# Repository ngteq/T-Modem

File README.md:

# T-Modem > USB-5V|12-Volt Terminal-Modem Reference
**Non-Profit for the Radio-World and easy to deploy/repair is parted by AI-Services**<br>
<br><br>

<br>

> **No firmware / no host software yet** — trees under `firmware/` and `software/` are placeholders only.  
> **Build a working hardware prototype first** (rails, assembly, bench checks).
> KiCad PCB is for **learning-by-doing** and small-run fab — run **DRC** and fix reported issues before ordering boards.  

**T-Modem** = **Terminal-Modem** — a real packet-radio modem board (registers + firmware) for host stacks such as MAX25-Stack.

**PHY mark:** **T-Modem-c12s24** — **c12** = chip **1200** (TCM3105-class AFSK) · **s24** = software **2400** (Pico firmware DSP later). One board; **no** second 2400 modem IC.

**Version:** **0.25** — hardware-only standard reference (**baseline** while building toward **v1.0**; software after the build) · [docs/HARDWARE-BASELINE.md](docs/HARDWARE-BASELINE.md)  
**License:** [GNU GPLv3](LICENSE)  
**Project intent:** non-profit / non-commercial community hardware project under GPLv3 (no separate legal entity claimed here).

**AS-IS — no support, no warranty:** This project and all materials are provided **as-is**. There is **no support** and **no warranty** of any kind. GPLv3 already disclaims warranty; this is also **project policy**.

**Scope:** T-Modem is a **standard reference only**. Custom product lines, per-customer variants, or commercial SKUs beyond that reference are **not** T-Modem — they are separate projects.

**Status/State:** The **v0.25** hardware design is **not** being redesigned. Develop it **as-is** to **v1.0** by **building** the board; **firmware / software come after** that. Change HW only if the build proves a blocking error.

Product docs and repo practice follow the operator publication standard (KISS, technical-right only, GPLv3 non-profit). This repository holds the complete product (hardware, firmware, shipped docs).

**Git branch:** you are on **`c12s24`** (active product tree). GitHub **`main`** is an index only — see [BRANCHES.md](BRANCHES.md).

---

## v0.25 release (this tag)

| Ships | Does not ship |
|-------|----------------|
| BOM with preferred commodity candidates + longevity notes | Firmware / host software |
| Fabricable netlist + KiCad project (190×110 mm TH PCB) | Fab-verified Gerbers without DRC pass |
| PCB outline + placement + assembly notes | Invented radio mic pinouts |
| Power · USB-A · green LCD · Pico UF2 · **TCM3105-class AFSK IF**
| **Hobby-friendly soldering** (sockets + through-hole) | Reflow / fine-pitch SMD as the default path |

See [docs/RELEASE-v0.25.md](docs/RELEASE-v0.25.md) · [docs/v0.25-VERIFICATION.md](docs/v0.25-VERIFICATION.md) · [docs/BOM.md](docs/BOM.md) · [docs/SCHEMATIC.md](docs/SCHEMATIC.md) · [docs/PCB-ASSEMBLY.md](docs/PCB-ASSEMBLY.md) · [hardware/](hardware/).

**Firmware / software:** placeholders only — [firmware/README.md](firmware/README.md) · [software/README.md](software/README.md).

---

## Hobby-friendly soldering

v0.25 is aimed at **hand soldering for anyone who can solder reasonably well** — not only professional reflow lines. Goal: **best value for money**, socketed, replaceable parts.

| Practice | Intent |
|----------|--------|
| **DIP / module sockets** | Modem IC in a **16-pin DIP socket**; Pico and LCD on **2.54 mm female sockets** |
| **Through-hole first** | Resistors, diodes, LEDs, trimmers, USB-A, barrel jack, screw terminals — **TH** (cheap commodity packs) |
| **Pre-made cheap modules** | Pico (~few €), green 16×2 LCD module, MP1584-class buck module — plug in, no fine-pitch MCU soldering |
| **I²C LCD level shift** | 5 V LCD1602 I²C backpack ↔ Pico 3.3 V: BSS138-class 4-ch module (**LV=3.3 V** · **HV=5 V** · GND common) — see [docs/BOM.md](docs/BOM.md) `U_LVL` |
| **Not required** | Stencil reflow, QFN/BGA, expensive milled sockets, or SOIC as the only modem package |

Assembly and cheap-part notes: [docs/PCB-ASSEMBLY.md](docs/PCB-ASSEMBLY.md) · [docs/BOM.md](docs/BOM.md) · [docs/ORDERING-BUDGET.md](docs/ORDERING-BUDGET.md).

---

## Role

| This repo | Elsewhere |
|-----------|-----------|
| Complete T-Modem **standard reference**: hardware, (future) firmware, BOM/PCB, shipped docs | MAX25-Stack: **thin plugin only** later (discover / talk; host keeps AX.25 / KISS) |
| Board owns modem PHY + register file + thin KISS bridge (when FW exists)

**Settled scope**

| Item | Fact |
|------|------|
| Form | Rectangle **190 × 110 mm** (v0.25 outline; §0.26 larger OK) |
| Modulation | AFSK **1200** (TCM3105-class) + **2400** (MCU DSP, FW later) |
| Host link | USB 2.0 **Type A receptacle** (toward PC); no active hub required |
| Power | **USB-only OK**; barrel **12 V** + buck **optional** (on reference); USB OR; optional active hub / **5 V** into USB/OR rail |
| Display | HD44780-class **16×2** character LCD, **green backlight** (preferred) |
| MCU | **Raspberry Pi Pico** (RP2040), preferably **Pico H** on socketed headers — ROM **UF2** field flash |
| Modem IC | **TCM3105**-class Bell-202 in **DIP + socket**
| Assembly | **Hobby-friendly:** sockets + through-hole; see section above |
| Field flash | Via the **USB Type-A** port to the PC (when FW exists) |
| Layer split | Host owns AX.25; board = modem + thin KISS |
| Radio equipment | Screw-terminal AF/PTT labels only — **no** invented mic pinouts |

---

## Build

| Step | v0.25 status |
|------|----------------|
| Schematic / netlist | **Documented** — [docs/SCHEMATIC.md](docs/SCHEMATIC.md) |
| KiCad project | **Present** — [hardware/kicad/t-modem/](hardware/kicad/t-modem/) (KiCad ≥8; docs images via `scripts/render_docs_images.py`) |
| PCB outline / placement | **Documented** — [docs/PCB-ASSEMBLY.md](docs/PCB-ASSEMBLY.md) · [docs/PCB-LAYOUT.md](docs/PCB-LAYOUT.md) |
| BOM | **Candidates** — [docs/BOM.md](docs/BOM.md) · [hardware/bom/BOM.csv](hardware/bom/BOM.csv) |
| Verification | [docs/v0.25-VERIFICATION.md](docs/v0.25-VERIFICATION.md) |
| Firmware tree | **Placeholder only** |
| Fab | **DRC clean** → export Gerbers — see [hardware/fab/README.md](hardware/fab/README.md). Personal small-run OK — **AS-IS** |

---

## Operate

| Topic | Status |
|-------|--------|
| Host attach (USB CDC/ACM) | **TBD** until firmware |
| Register map / KISS | **TBD** — see [docs/OVERVIEW.md](docs/OVERVIEW.md) |
| Radio cable / pinout per model | **TBD** — expand from verified notes only |
| RX before live TX | Operator practice when RF path exists |

Site-private secrets belong in `./local/` (gitignored) — never commit passwords or host inventories.

---

## Documentation

| Doc | Content |
|-----|---------|
| [docs/README.md](docs/README.md) | Doc index |
| [docs/RELEASE-v0.25.md](docs/RELEASE-v0.25.md) | v0.25 hardware-only release note |
| [docs/v0.25-VERIFICATION.md](docs/v0.25-VERIFICATION.md) | Self-audit checklist |
| [docs/BOM.md](docs/BOM.md) | Bill of materials (candidates + sockets / TH hobby path) |
| [docs/ORDERING-BUDGET.md](docs/ORDERING-BUDGET.md) | Budget buy list — cheap, socketed, hand-solder |
| [docs/SCHEMATIC.md](docs/SCHEMATIC.md) | Fabricable netlist + block diagram |
| [docs/PCB-ASSEMBLY.md](docs/PCB-ASSEMBLY.md) | Outline, placement, hobby-friendly assembly |
| [docs/OVERVIEW.md](docs/OVERVIEW.md) | Settled product facts |
| [docs/HARDWARE-INTENT.md](docs/HARDWARE-INTENT.md) | Form, interfaces, radio intent |

Uncertain items are marked **TBD**. Do not treat TBD as verified capability.

---

## License and project intent

Copyright and distribution terms: **GNU General Public License v3** — see [LICENSE](LICENSE).

This is a **non-profit** open hardware / firmware project: share and change under GPLv3; not a commercial product pitch.

**AS-IS:** provided without support and without warranty of any kind (see notice at top of this README and GPLv3 §§15–16).

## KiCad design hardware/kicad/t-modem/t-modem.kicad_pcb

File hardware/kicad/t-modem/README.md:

# KiCad project — T-Modem v0.25

Open **`t-modem.kicad_pro`** in **KiCad ≥ 8** (tested with **KiCad 10**).

| File | Role |
|------|------|
| `t-modem.kicad_pro` | Project |
| `t-modem.kicad_sch` | Schematic + embedded symbols |
| `t-modem.kicad_sym` | Custom TCM3105 + Pico subset |
| `t-modem.kicad_pcb` | **190×110 mm** board — copper DRC short/unconn/cross **0/0/0** (prototype-ready) |
| `sym-lib-table` | Points at `t-modem.kicad_sym` |

## Operator steps

1. Open **`t-modem.kicad_pro`** → run **DRC**.  
2. Silk cosmetic warnings may remain (`silk_over_copper` / overlap) — OK for prototype.  
3. Export Gerbers + drill — see [`../../fab/README.md`](../../fab/README.md).

**Authoritative electrical design:** [`../../../docs/SCHEMATIC.md`](../../../docs/SCHEMATIC.md)  
**Assembly:** [`../../../docs/PCB-ASSEMBLY.md`](../../../docs/PCB-ASSEMBLY.md)

**AS-IS:** no support, no warranty · GPLv3 · standard reference only · **not** BayCom/SER12.

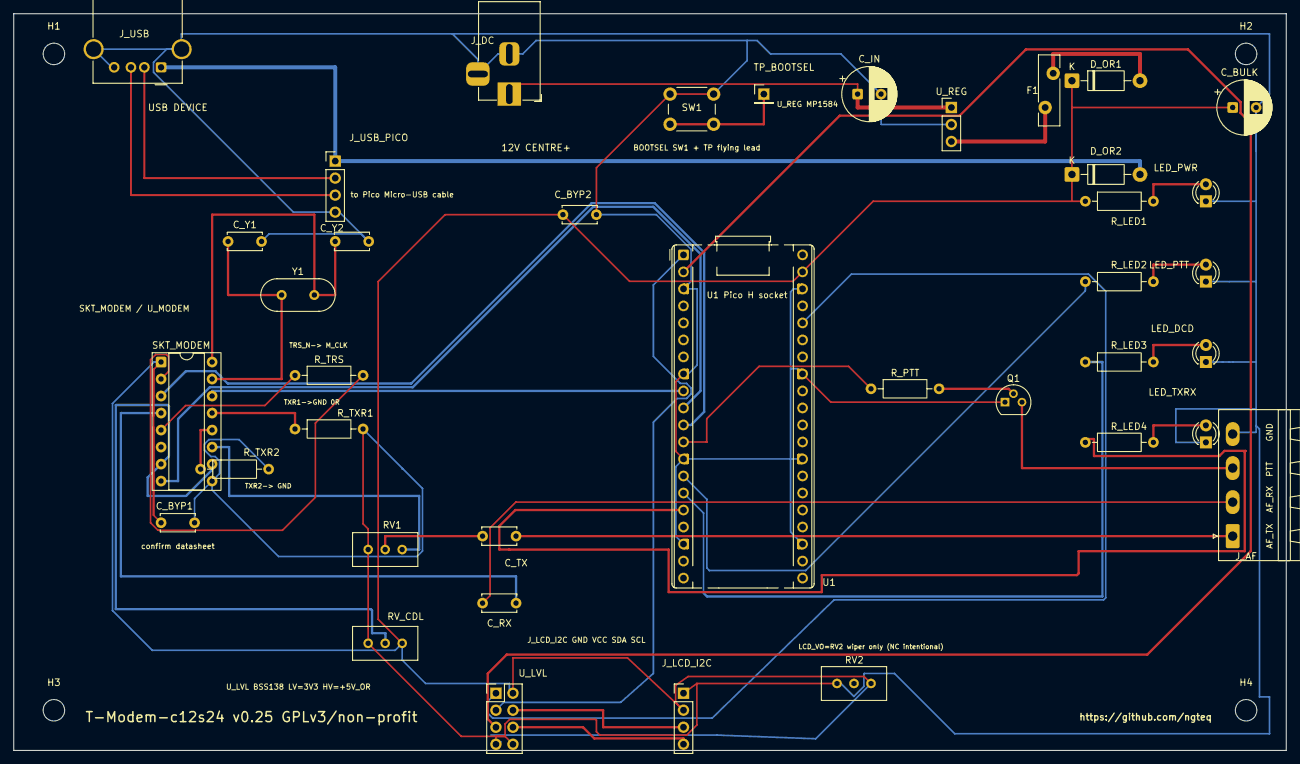
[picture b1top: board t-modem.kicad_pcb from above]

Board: 2 copper layers, 190.0 x 110.0 mm, 43 parts (0 on the bottom side), 39 nets.

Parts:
C_BULK: 100uF; CP_Radial_D8.0mm_P3.50mm
C_BYP1, C_BYP2: 100nF; C_Disc_D5.0mm_W2.5mm_P5.00mm
C_IN: 100uF; CP_Radial_D8.0mm_P3.50mm
C_RX: 100nF; C_Disc_D5.0mm_W2.5mm_P5.00mm
C_TX: 100nF; C_Disc_D5.0mm_W2.5mm_P5.00mm
C_Y1, C_Y2: 22pF; C_Disc_D5.0mm_W2.5mm_P5.00mm
D_OR1, D_OR2: 1N5819; D_DO-41_SOD81_P10.16mm_Horizontal
F1: MF-RG500; Fuse_Bourns_MF-RG500
H1, H2, H3, H4: M3; MountingHole_3.2mm_M3
J_AF: AF; PhoenixContact_MSTBA_2,5_4-G-5,08_1x04_P5.08mm_Horizontal
J_DC: 12V CENTRE+; BarrelJack_Horizontal
J_LCD_I2C: LCD I2C; PinHeader_1x04_P2.54mm_Vertical
J_USB: USB_A; USB_A_Molex_67643_Horizontal
J_USB_PICO: to Pico Micro-USB cable; PinHeader_1x04_P2.54mm_Vertical
LED_DCD: DCD; LED_D3.0mm
LED_PTT: PTT; LED_D3.0mm
LED_PWR: PWR; LED_D3.0mm
LED_TXRX: TXRX; LED_D3.0mm
Q1: 2N2222A; TO-92
RV1: 10k TX; Potentiometer_Bourns_3296W_Vertical
RV2: 10k contrast; Potentiometer_Bourns_3296W_Vertical
RV_CDL: 50k CDL; Potentiometer_Bourns_3296W_Vertical
R_LED1, R_LED2, R_LED3, R_LED4: 1k; R_Axial_DIN0207_L6.3mm_D2.5mm_P10.16mm_Horizontal
R_PTT: 4.7k; R_Axial_DIN0207_L6.3mm_D2.5mm_P10.16mm_Horizontal
R_TRS: 0R; R_Axial_DIN0207_L6.3mm_D2.5mm_P10.16mm_Horizontal
R_TXR1, R_TXR2: 0R; R_Axial_DIN0207_L6.3mm_D2.5mm_P10.16mm_Horizontal
SKT_MODEM: U_MODEM TCM3105; DIP-16_W7.62mm_Socket
SW1: BOOTSEL; SW_PUSH_6mm
TP_BOOTSEL: to Pico BOOTSEL; PinHeader_1x01_P2.54mm_Vertical
U1: RaspberryPi_Pico; RaspberryPi_Pico_Common_THT
U_LVL: BSS138; PinHeader_2x04_P2.54mm_Vertical
U_REG: MP1584 VIN GND 5V; PinHeader_1x03_P2.54mm_Vertical
Y1: 4.433619; Crystal_HC49-U_Vertical

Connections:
3V3: U1.36, U_LVL.1
+5V: D_OR1.2, F1.2
+5V_OR: C_BULK.1, C_BYP1.1, C_BYP2.1, D_OR1.1, D_OR2.1, J_LCD_I2C.2, RV2.1, RV_CDL.1, R_LED1.1, SKT_MODEM.1, U1.39, U_LVL.2
+5V_REG: F1.1, U_REG.3
AF_RX: C_RX.1, J_AF.2
AF_TX: C_TX.2, J_AF.1
BOOTSEL: SW1.2, TP_BOOTSEL.1
CDL: RV_CDL.2, SKT_MODEM.7, SKT_MODEM.10
GND: C_BULK.2, C_BYP1.2, C_BYP2.2, C_IN.2, C_Y1.2, C_Y2.2, J_AF.4, J_DC.2, J_DC.3, J_LCD_I2C.1, J_USB.4, J_USB.SH, J_USB_PICO.4, LED_DCD.1, LED_PTT.1, LED_PWR.1, LED_TXRX.1, Q1.1, RV1.3, RV2.3, RV_CDL.3, R_TXR1.2, R_TXR2.2, SKT_MODEM.9, SW1.1, U1.3, U1.8, U1.13, U1.18, U1.23, U1.28, U1.33, U1.38, U_LVL.7, U_LVL.8, U_REG.2
I2C_SCL_3V3: U1.2, U_LVL.5
I2C_SCL_5V: J_LCD_I2C.4, U_LVL.6
I2C_SDA_3V3: U1.1, U_LVL.3
I2C_SDA_5V: J_LCD_I2C.3, U_LVL.4
LED_DCD_A: LED_DCD.2, R_LED3.2
LED_DCD_N: R_LED3.1, U1.15
LED_PTT_A: LED_PTT.2, R_LED2.2
LED_PTT_N: R_LED2.1, U1.14
LED_PWR_A: LED_PWR.2, R_LED1.2
LED_TXRX_A: LED_TXRX.2, R_LED4.2
LED_TXRX_N: R_LED4.1, U1.16
MODEM_CDT: SKT_MODEM.3, U1.11
MODEM_CLK: R_TRS.2, SKT_MODEM.2
MODEM_RXD: SKT_MODEM.8, U1.10
MODEM_TXD: SKT_MODEM.14, U1.9
OSC1: C_Y1.1, SKT_MODEM.15, Y1.1
OSC2: C_Y2.1, SKT_MODEM.16, Y1.2
PTT_B: Q1.2, R_PTT.2
PTT_DRV: R_PTT.1, U1.12
PTT_OC: J_AF.3, Q1.3
RXA: C_RX.2, SKT_MODEM.4
TRS_N: R_TRS.1, SKT_MODEM.5
TXA: RV1.1, SKT_MODEM.11
TXR1_N: R_TXR1.1, SKT_MODEM.13
TXR2_N: R_TXR2.1, SKT_MODEM.12
TX_LVL: C_TX.1, RV1.2
USB_DM: J_USB.2, J_USB_PICO.2
USB_DP: J_USB.3, J_USB_PICO.3
VBUS: D_OR2.2, J_USB.1, J_USB_PICO.1
VIN_12: C_IN.1, J_DC.1, U_REG.1

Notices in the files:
hardware/kicad/t-modem/t-modem.kicad_pcb:
GPLv3/non-profit (as-is)
T-Modem-c12s24 v0.25 GPLv3/non-profit
